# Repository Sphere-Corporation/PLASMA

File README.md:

## Documentation

The documentation for this project is hosted in a Google Drive [here](https://drive.google.com/drive/folders/1ESX8Nsf-v13hcnTwWp5Z_RH3zX6Ep41N?usp=sharing)

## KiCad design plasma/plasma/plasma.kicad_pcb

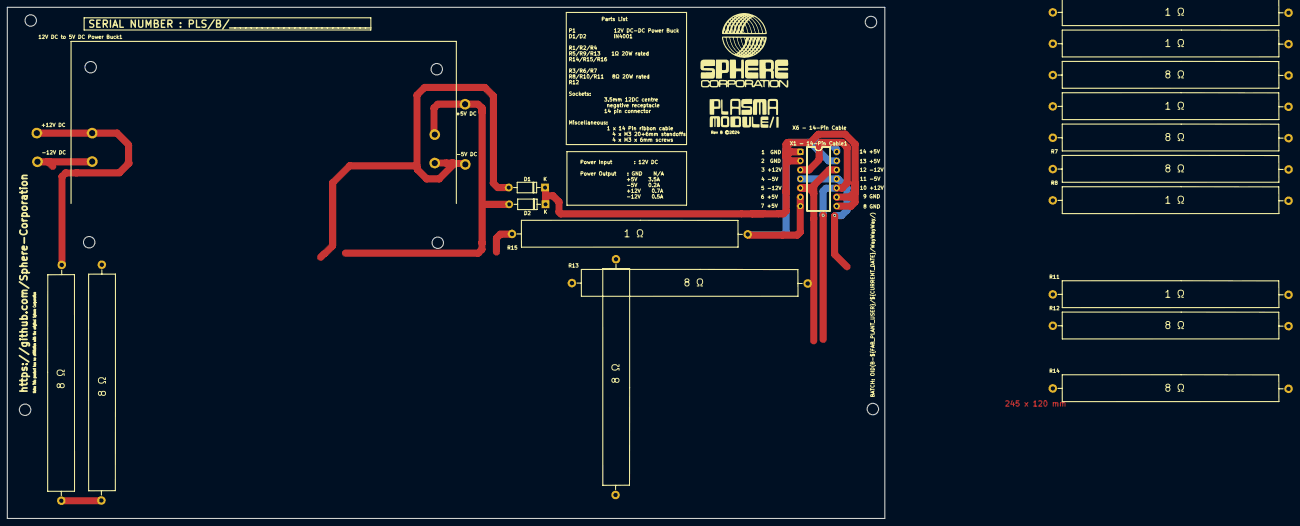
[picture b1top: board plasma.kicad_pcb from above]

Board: 2 copper layers, 245.7 x 143.1 mm, 20 parts (0 on the bottom side), 17 nets.

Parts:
12V DC to 5V DC Power Buck1: Weewooday Adjustable LM2596S DC-DC Buck Converter
D1, D2: 1N4001; D_DO-41_SOD81_P10.16mm_Horizontal
R1, R2, R4, R8, R11, R15: 1 Ω; R_Axial_DIN0411_L60.0mm_D10mm_P15.24mm_Horizontal 20Watt 8O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
R3, R5, R6, R7, R9, R10, R12, R13, R14: 8 Ω; R_Axial_DIN0411_L60.0mm_D10mm_P15.24mm_Horizontal 20Watt 8O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
X1 - 14-Pin Cable1, X6 - 14-Pin Cable: 14-Pin Cable; DIP-14_W10.16mm

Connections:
+12V: R9.1, R9.2, R10.2
/+12VDC: R11.2, X1 - 14-Pin Cable1.3, X1 - 14-Pin Cable1.10, X6 - 14-Pin Cable.3, X6 - 14-Pin Cable.10
/-12VDC: R14.2, X1 - 14-Pin Cable1.5, X1 - 14-Pin Cable1.12
/GND: D1.1 (K), D2.1 (K), X1 - 14-Pin Cable1.1, X1 - 14-Pin Cable1.2, X1 - 14-Pin Cable1.8, X1 - 14-Pin Cable1.9
unnamed: D1.2 (A), R1.1, R2.1, R3.1
unnamed: D2.2 (A), R5.1
unnamed: X6 - 14-Pin Cable.1, X6 - 14-Pin Cable.2, X6 - 14-Pin Cable.8, X6 - 14-Pin Cable.9
unnamed: R1.2, R2.2, R3.2, R4.1
unnamed: R4.2, X1 - 14-Pin Cable1.6, X1 - 14-Pin Cable1.7, X1 - 14-Pin Cable1.13, X1 - 14-Pin Cable1.14
unnamed: R5.2, R6.1
unnamed: R6.2, R7.1
unnamed: R7.2, R8.1
unnamed: R8.2, X1 - 14-Pin Cable1.4, X1 - 14-Pin Cable1.11
unnamed: R12.2, R13.1, X6 - 14-Pin Cable.5, X6 - 14-Pin Cable.12
unnamed: R13.2, R14.1
unnamed: R15.2, X6 - 14-Pin Cable.6, X6 - 14-Pin Cable.7, X6 - 14-Pin Cable.13, X6 - 14-Pin Cable.14
unnamed: X6 - 14-Pin Cable.4, X6 - 14-Pin Cable.11

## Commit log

2024-03-04 Initial commit of Project Plasma
2024-03-04 Added .gitignore
2024-04-02 Final commit before disassociating from combined repo
2025-01-01 Initial re-baselined commit

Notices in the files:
plasma/plasma/plasma.kicad_pcb:
Rev B ©2024
